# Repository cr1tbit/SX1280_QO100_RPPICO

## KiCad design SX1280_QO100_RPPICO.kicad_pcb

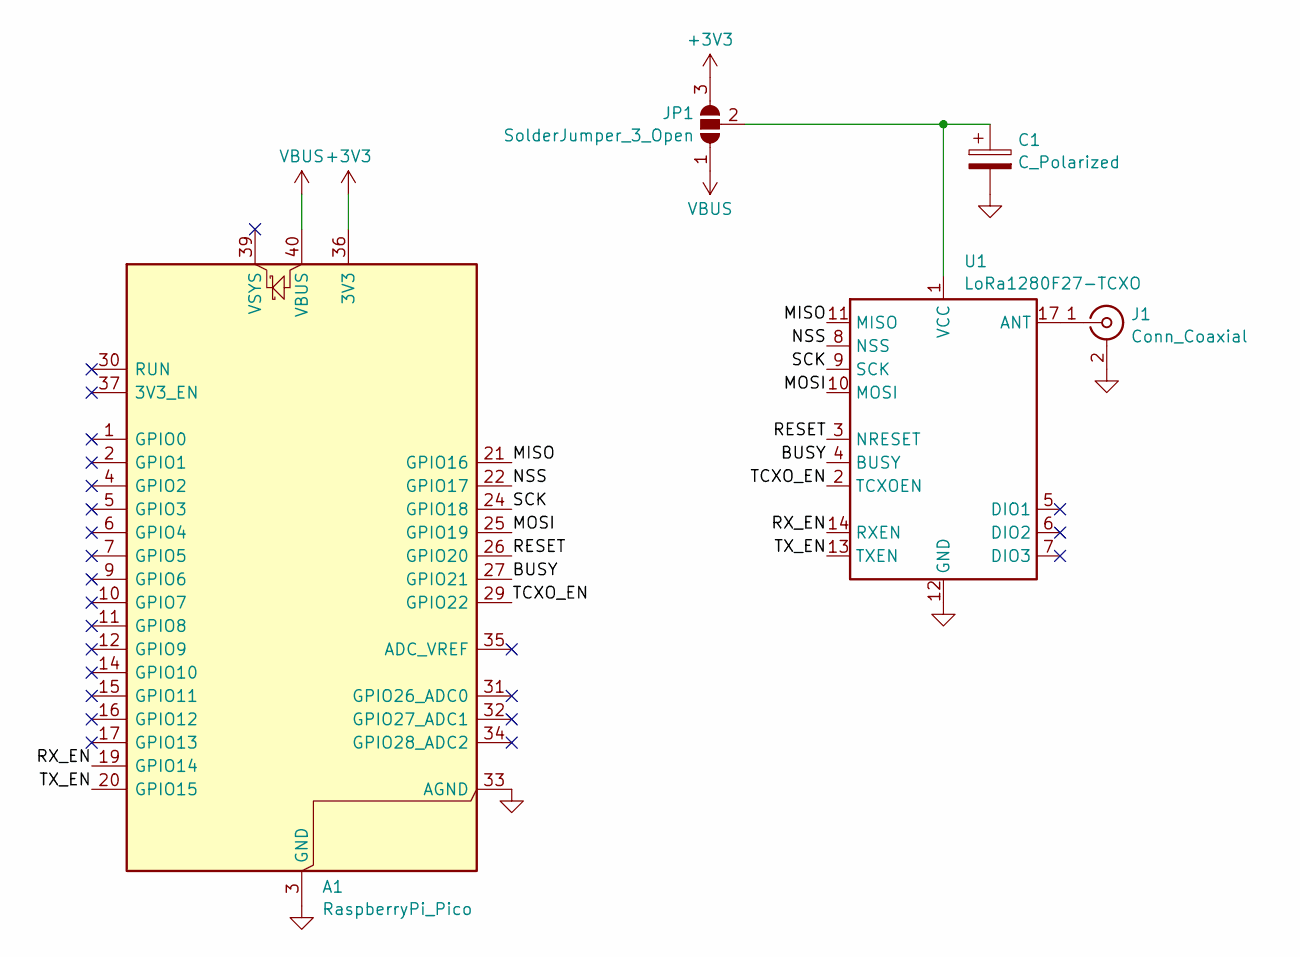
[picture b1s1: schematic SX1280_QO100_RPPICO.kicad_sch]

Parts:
A1: RaspberryPi_Pico; RaspberryPi_Pico_Common_Unspecified
C1: C_Polarized; C_1210_3225Metric_Pad1.33x2.70mm_HandSolder
J1: Conn_Coaxial; SMA_BAT_Wireless_BWSMA-KWE-Z001
JP1: SolderJumper_3_Open; SolderJumper-3_P2.0mm_Open_TrianglePad1.0x1.5mm
U1: LoRa1280F27-TCXO; LORA1280F27-TCXO; Manufacturer Part LoRa1280F27-TCXO

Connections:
+3V3: A1.36 (3V3), JP1.3 (B)
/BUSY: A1.27 (GPIO21), U1.4 (BUSY)
/MISO: A1.21 (GPIO16), U1.11 (MISO)
/MOSI: A1.25 (GPIO19), U1.10 (MOSI)
/NSS: A1.22 (GPIO17), U1.8 (NSS)
/RESET: A1.26 (GPIO20), U1.3 (NRESET)
/RX_EN: A1.19 (GPIO14), U1.14 (RXEN)
/SCK: A1.24 (GPIO18), U1.9 (SCK)
/TCXO_EN: A1.29 (GPIO22), U1.2 (TCXOEN)
/TX_EN: A1.20 (GPIO15), U1.13 (TXEN)
GND: A1.3 (GND), A1.8 (GND), A1.13 (GND), A1.18 (GND), A1.23 (GND), A1.28 (GND), A1.33 (AGND), A1.38 (GND), C1.2, J1.2 (Ext), U1.12 (GND), U1.15 (GND), U1.16 (GND), U1.18 (GND)
unnamed: J1.1 (In), U1.17 (ANT)
unnamed: C1.1, JP1.2 (C), U1.1 (VCC)
VBUS: A1.40 (VBUS), JP1.1 (A)

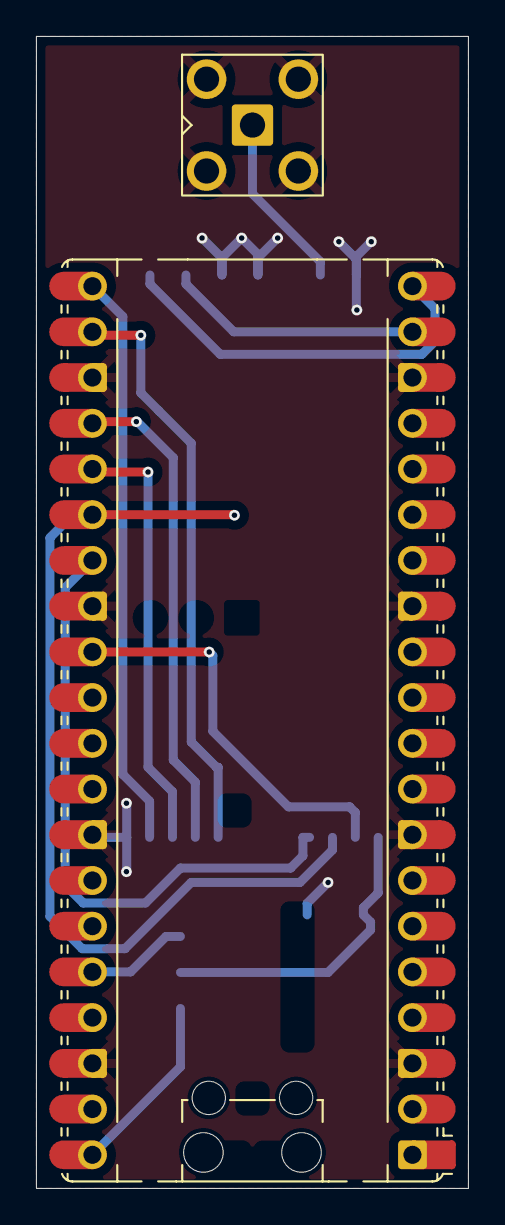
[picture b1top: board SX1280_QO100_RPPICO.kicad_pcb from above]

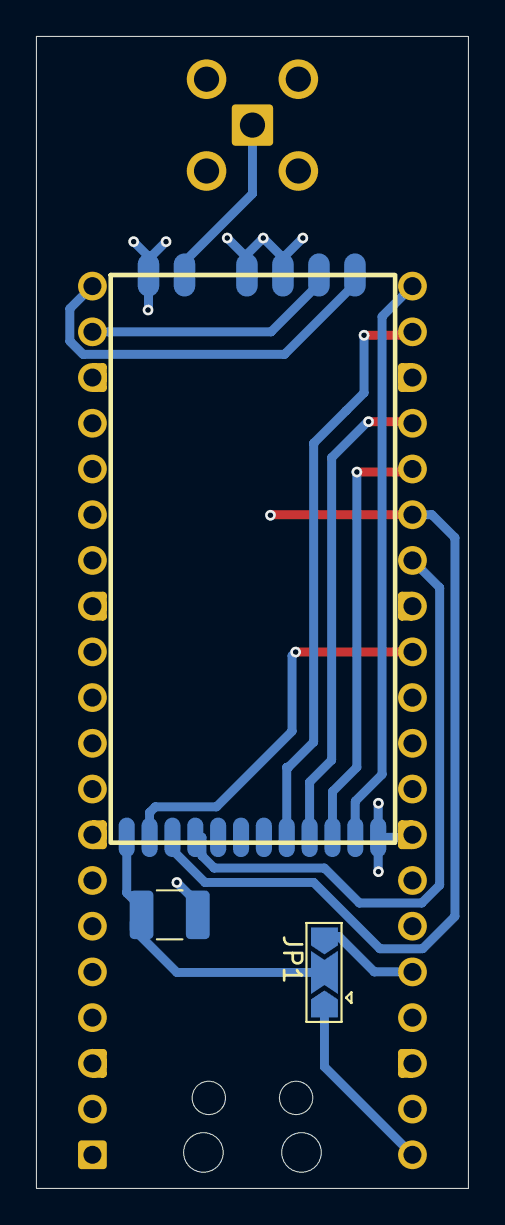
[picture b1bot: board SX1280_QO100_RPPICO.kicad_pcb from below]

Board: 2 copper layers, 24.0 x 64.0 mm, 5 parts (3 on the bottom side), 14 nets.

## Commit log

2026-01-22 add files
